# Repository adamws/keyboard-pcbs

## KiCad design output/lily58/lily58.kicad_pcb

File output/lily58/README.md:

## lily58/lily58

[layout](lily58-kle.json) - [PCB](lily58.kicad_pcb)

{:loading="lazy"}

[Open in keyboard-layout-editor](http://www.keyboard-layout-editor.com/##@@_x:3.5;&=0,3&_x:8.5;&=5,3;&@_x:2.5&y:-0.875;&=0,2&_x:1.0;&=0,4&_x:6.5;&=5,4&_x:1.0;&=5,2;&@_x:5.5&y:-0.875;&=0,5&_x:4.5;&=5,5;&@_x:1.5&y:-0.875;&=0,1&_x:12.5;&=5,1;&@_x:0.5&y:-0.875&c=#777777;&=0,0&_x:14.5&c=#cccccc;&=5,0;&@_x:3.5&y:-0.5;&=1,3&_x:8.5;&=6,3;&@_x:2.5&y:-0.875;&=1,2&_x:1.0;&=1,4&_x:6.5;&=6,4&_x:1.0;&=6,2;&@_x:5.5&y:-0.875;&=1,5&_x:4.5;&=6,5;&@_x:1.5&y:-0.875;&=1,1&_x:12.5;&=6,1;&@_x:0.5&y:-0.875&c=#aaaaaa;&=1,0&_x:14.5&c=#cccccc;&=6,0;&@_x:3.5&y:-0.5;&=2,3&_x:8.5;&=7,3;&@_x:2.5&y:-0.875;&=2,2&_x:1.0;&=2,4&_x:6.5;&=7,4&_x:1.0;&=7,2;&@_x:5.5&y:-0.875;&=2,5&_x:4.5;&=7,5;&@_x:1.5&y:-0.875;&=2,1&_x:12.5;&=7,1;&@_x:0.5&y:-0.875&c=#aaaaaa;&=2,0&_x:14.5&c=#cccccc;&=7,0;&@_x:6.5&y:-0.75;&=4,5&_x:2.5;&=9,5;&@_x:3.5&y:-0.75;&=3,3&_x:8.5;&=8,3;&@_x:2.5&y:-0.875;&=3,2&_x:1.0;&=3,4&_x:6.5;&=8,4&_x:1.0;&=8,2;&@_x:5.5&y:-0.875;&=3,5&_x:4.5;&=8,5;&@_x:1.5&y:-0.875;&=3,1&_x:12.5;&=8,1;&@_x:0.5&y:-0.875&c=#aaaaaa;&=3,0&_x:14.5;&=8,0;&@_x:3&y:-0.375;&=4,1;&@_x:4&y:-0.975;&=4,2&_x:7.5;&=9,2&=9,1;&@_x:5&y:-0.9;&=4,3&_x:0.5&c=#777777&h:1.5;&=4,4&_x:2.5&h:1.5;&=9,4&_x:0.5&c=#aaaaaa;&=9,3)

{:loading="lazy"}

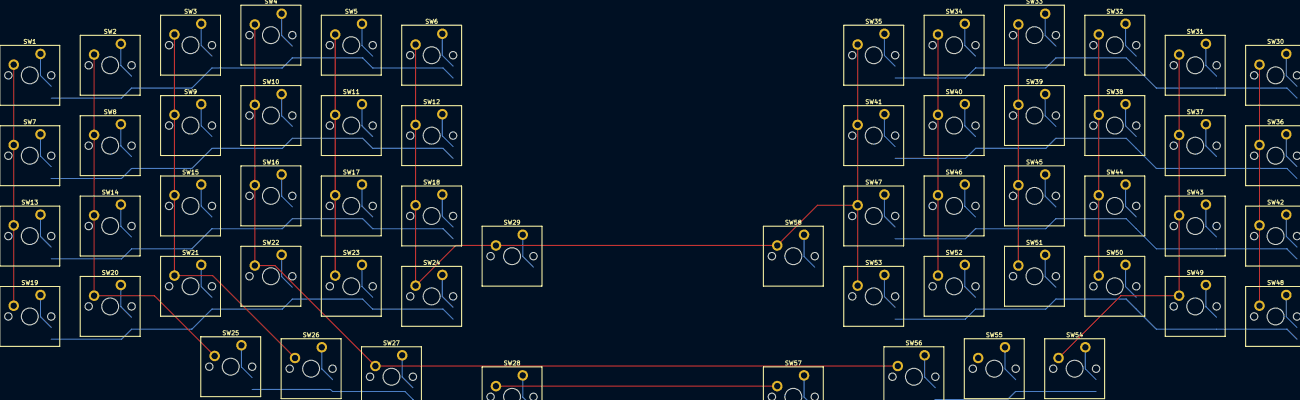
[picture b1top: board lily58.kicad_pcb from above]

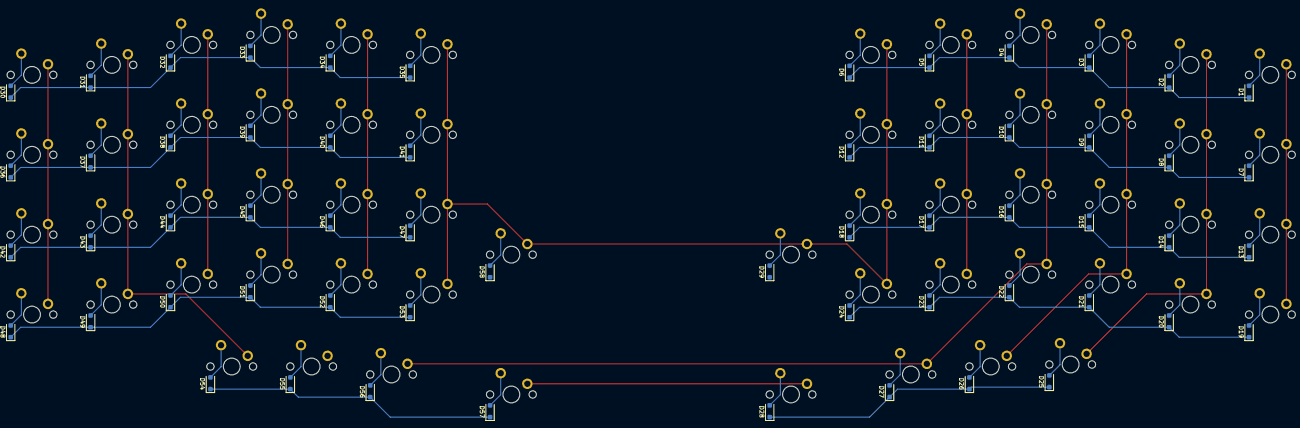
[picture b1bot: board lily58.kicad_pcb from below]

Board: 2 copper layers, 116 parts (58 on the bottom side), 74 nets.

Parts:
D1, D2, D3, D4, D5, D6, D7, D8, D9, D10, D11, D12, D13, D14, D15, D16, D17, D18, D19, D20, D21, D22, D23, D24, D25, D26, D27, D28, D29, D30, D31, D32, D33, D34, D35, D36, D37, D38, D39, D40, D41, D42, D43, D44, D45, D46, D47, D48, D49, D50, D51, D52, D53, D54, D55, D56, D57, D58: D_SOD-123F
SW1, SW2, SW3, SW4, SW5, SW6, SW7, SW8, SW9, SW10, SW11, SW12, SW13, SW14, SW15, SW16, SW17, SW18, SW19, SW20, SW21, SW22, SW23, SW24, SW25, SW26, SW27, SW28, SW29, SW30, SW31, SW32, SW33, SW34, SW35, SW36, SW37, SW38, SW39, SW40, SW41, SW42, SW43, SW44, SW45, SW46, SW47, SW48, SW49, SW50, SW51, SW52, SW53, SW54, SW55, SW56, SW57, SW58: SW_Cherry_MX_PCB_1.00u

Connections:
COL0: SW1.1, SW7.1, SW13.1, SW19.1, SW30.1, SW36.1, SW42.1, SW48.1
COL1: SW2.1, SW8.1, SW14.1, SW20.1, SW25.1, SW31.1, SW37.1, SW43.1, SW49.1, SW54.1
COL2: SW3.1, SW9.1, SW15.1, SW21.1, SW26.1, SW32.1, SW38.1, SW44.1, SW50.1, SW55.1
COL3: SW4.1, SW10.1, SW16.1, SW22.1, SW27.1, SW33.1, SW39.1, SW45.1, SW51.1, SW56.1
COL4: SW5.1, SW11.1, SW17.1, SW23.1, SW28.1, SW34.1, SW40.1, SW46.1, SW52.1, SW57.1
COL5: SW6.1, SW12.1, SW18.1, SW24.1, SW29.1, SW35.1, SW41.1, SW47.1, SW53.1, SW58.1
unnamed: D1.2, SW1.2
unnamed: D2.2, SW2.2
unnamed: D3.2, SW3.2
unnamed: D4.2, SW4.2
unnamed: D5.2, SW5.2
unnamed: D6.2, SW6.2
unnamed: D7.2, SW7.2
unnamed: D8.2, SW8.2
unnamed: D9.2, SW9.2
unnamed: D10.2, SW10.2
unnamed: D11.2, SW11.2
unnamed: D12.2, SW12.2
unnamed: D13.2, SW13.2
unnamed: D14.2, SW14.2
unnamed: D15.2, SW15.2
unnamed: D16.2, SW16.2
unnamed: D17.2, SW17.2
unnamed: D18.2, SW18.2
unnamed: D19.2, SW19.2
unnamed: D20.2, SW20.2
unnamed: D21.2, SW21.2
unnamed: D22.2, SW22.2
unnamed: D23.2, SW23.2
unnamed: D24.2, SW24.2
unnamed: D25.2, SW25.2
unnamed: D26.2, SW26.2
unnamed: D27.2, SW27.2
unnamed: D28.2, SW28.2
unnamed: D29.2, SW29.2
unnamed: D30.2, SW30.2
unnamed: D31.2, SW31.2
unnamed: D32.2, SW32.2
unnamed: D33.2, SW33.2
unnamed: D34.2, SW34.2
unnamed: D35.2, SW35.2
unnamed: D36.2, SW36.2
unnamed: D37.2, SW37.2
unnamed: D38.2, SW38.2
unnamed: D39.2, SW39.2
unnamed: D40.2, SW40.2
unnamed: D41.2, SW41.2
unnamed: D42.2, SW42.2
unnamed: D43.2, SW43.2
unnamed: D44.2, SW44.2
unnamed: D45.2, SW45.2
unnamed: D46.2, SW46.2
unnamed: D47.2, SW47.2
unnamed: D48.2, SW48.2
unnamed: D49.2, SW49.2
unnamed: D50.2, SW50.2
unnamed: D51.2, SW51.2
unnamed: D52.2, SW52.2
unnamed: D53.2, SW53.2
unnamed: D54.2, SW54.2
unnamed: D55.2, SW55.2
unnamed: D56.2, SW56.2
unnamed: D57.2, SW57.2
unnamed: D58.2, SW58.2
ROW0: D1.1, D2.1, D3.1, D4.1, D5.1, D6.1
ROW1: D7.1, D8.1, D9.1, D10.1, D11.1, D12.1
ROW2: D13.1, D14.1, D15.1, D16.1, D17.1, D18.1
ROW3: D19.1, D20.1, D21.1, D22.1, D23.1, D24.1
ROW4: D25.1, D26.1, D27.1, D28.1, D29.1
ROW5: D30.1, D31.1, D32.1, D33.1, D34.1, D35.1
ROW6: D36.1, D37.1, D38.1, D39.1, D40.1, D41.1
ROW7: D42.1, D43.1, D44.1, D45.1, D46.1, D47.1
ROW8: D48.1, D49.1, D50.1, D51.1, D52.1, D53.1
ROW9: D54.1, D55.1, D56.1, D57.1, D58.1
